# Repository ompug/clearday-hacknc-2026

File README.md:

# Clearday

A social money app for roommates, built at HackNC 2026. Upcoming bills float as glossy Frutiger Aero bubbles you pop when they are paid. Shared expenses split through a real ledger and update live for everyone in the household. A Monte Carlo "money weather" forecast warns of tight weeks before they happen, and Clearday Home (an Arduino UNO Q with a smart bulb) reacts to the household in real time.

Clearday is an independent hackathon project. It is not affiliated with or endorsed by Capital One. The demo runs entirely on seeded sandbox and synthetic data.

## What it does

- **The sky.** Each bill is a bubble; height shows how soon it is due and the icon plus label shows whether the forecast says you can cover it. A list view is the screen-reader default.
- **Live shared bubbles.** Rent, electric and internet are shared. Popping a share pays through a Nessie transfer and the ledger; every roommate's screen (and the bulb) updates over Socket.IO.
- **Money weather.** A 30-day forecast with a plain-words chance of dipping below your cushion, safe-to-spend, and a labeled backtest number.
- **Split with words.** "Split last night's pizza with Jake and Priya": Gemma finds the purchase through narrow tools, the server computes every amount, and you confirm.
- **Receipt itemizing and price memory.** Scan a receipt, fix the items, split by item with tax and tip, and see "cheaper before" hints.
- **Also built:** unusual-charge and duplicate-subscription detection, an ElevenLabs household announcement with transcript, a weekly recap, an amount-free private feed, a hypothetical 10-year Future view, a synthetic-household analyst view, and a private opt-in help panel with NC resources.

| Forecast | Split proposal |
| --- | --- |
|  |  |

| Receipt split | List view | Private feed |
| --- | --- | --- |
|  |  |  |

## Architecture

```
web/        Next.js + TypeScript + Tailwind + Framer Motion (responsive)
api/        FastAPI + python-socketio; owns every secret and external call
analytics/  Pure Python modules (forecast, categorize, detection, ...)
device/     Clearday Home: Linux-side Python (bulb, keypad, audio) + MCU sketch (LED matrix)
scripts/    dev.sh, seed_nessie.py, reset_demo.py, demo_rehearsal.py, E2E and audit tooling
docs/       Proposal, technical spec, security, hardware, build plan, demo script
```

- **web** talks only to the API (or an in-memory mock with `NEXT_PUBLIC_USE_MOCKS=1`).
- **api** is the only component that calls Nessie, Gemma and ElevenLabs. Nessie data is cached in the database; the demo reads from the cache.
- **Database:** TimescaleDB, local in podman/Docker (`docker-compose.yml`) for dev and the demo. A Tiger Cloud target (`DB_TARGET=tiger`) exists as an optional backup.
- **device** gets data only from `/api/device/summary` and `/api/household/status`, with a revocable device token. The bulb is driven through Home Assistant.
- **analytics:** `forecast`, `detection`, `backtest` and `synthetic_data` are the stats teammate's real models; `categorize`, `prices`, `cohorts` and `future` are still stubs returning deterministic data behind the exact contract signatures, and `splits` (the ledger math) is real.
- **Hosting:** local only. The demo runs the API, web and database on one laptop.

## Run it

Requires Python 3.12 (installed by bootstrap via uv), Node, and podman-compose or Docker Compose.

```bash
bash scripts/bootstrap.sh          # uv sync, git hooks (idempotent)
cp api/.env.example api/.env       # fill in your own keys; api/.env is gitignored
cp web/.env.example web/.env.local # set NEXT_PUBLIC_USE_MOCKS=0 to use the API
(cd web && npm install)
bash scripts/dev.sh up             # DB, API on :8000, web on :3001 (logs/ has output)
```

Other commands:

```bash
bash scripts/dev.sh status | down | restart
uv run python -m scripts.reset_demo        # return DB and Nessie records to the seeded state
bash scripts/dev.sh rehearse               # cold start, reset, walk every demo beat
uv run pytest && uv run ruff check         # Python tests and lint
(cd web && npm run check)                  # typecheck, lint, format
(cd device && uv sync && uv run pytest)    # device tests
```

`api/.env` holds the Nessie, ElevenLabs and model (Gemma, any OpenAI-compatible endpoint with tool calling) settings. Without a model endpoint the assistant falls back to a template; without ElevenLabs the announcement is text only.

## System design

Sources are in `docs/img/design/`; re-render with `uv run python docs/img/design/render.py`.

## Security and privacy

- **Money is integer cents everywhere.** Leftover cents use the largest-remainder method with ties broken by user ID, and totals reconcile to the cent. Nessie's whole-dollar amounts are converted only at the Nessie client boundary. `scripts/check_money.sh` lints for float money in the pre-commit hook.
- **Identity comes from the session cookie or device token**, never from request bodies or model output. Socket.IO connections without one are rejected.
- **Payments carry a client-generated idempotency key**, enforced by a unique constraint.
- **Model tool contract.** Gemma may call only `find_purchase`, `list_household_members`, `propose_split`, `explain_forecast`, `explain_anomaly` and `read_receipt`, with capped fields, rows and dates and at most 3 calls per request. It never sees raw history, account numbers, Nessie IDs or other people's real names. It proposes; the server recomputes every amount from the ledger; the user confirms. The audit log stores fields and row counts, never values. Merchant names, memos and receipt text are treated as untrusted data.
- **No amounts in the feed or on Clearday Home.** The device speaks household-level information only, without names by default.
- **Receipt images are deleted** right after extraction.
- **Secrets stay in `api/.env`** (gitignored); a pre-commit guard blocks staged secret values. Account views show a nickname and last 4 digits only.
- The analyst view uses synthetic households and hides segments under 20; the Future view is labeled "Hypothetical, not investment advice".

See `docs/03-security-and-privacy.md` for the full rules.

## Accessibility

WCAG AA contrast (audited on glass with axe via `scripts/ui_audit.py`), every bubble state has an icon and a text label, bubbles are real buttons with accessible names, full keyboard access with visible focus, a list view for screen readers, `prefers-reduced-motion` plus an in-app toggle, a text-size control that survives 200% zoom, and transcripts for all audio.

## Credits

- **Nessie**, Capital One's hackathon API, for the sandbox customers, accounts, purchases, bills and transfers.
- **ElevenLabs** for the household announcement and recap voices.
- **Google's Gemma** open model for natural-language splits and receipt reading.
- **TimescaleDB** (Tiger Data) for the time-series database.
- **Home Assistant** for driving the smart bulb.
- Built for HackNC 2026. Palette is inspired by, but not affiliated with, Capital One. All artwork is original.

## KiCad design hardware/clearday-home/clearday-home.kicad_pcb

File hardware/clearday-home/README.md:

# Clearday Home

Rev A, 2026-10-11, HackNC 2026. A USB-powered kitchen-counter companion for
the Clearday roommate bill-splitting app. It uses light and short spoken
announcements, with no display and no dollar amounts shown on the device.

Open **`clearday-home.kicad_pro` in KiCad 8**. The five-sheet schematic, BOM,
and PDF are complete. The 70 mm PCB is an **unrouted placement study, not a
manufacturing release**. The board and review Gerbers must not be fabricated.

## Files and verification

- `clearday-home.kicad_sch`: Power & USB and links to four child sheets.
- `mcu.kicad_sch`, `leds.kicad_sch`, `audio.kicad_sch`, `inputs.kicad_sch`:
  MCU, LEDs, Audio, and Inputs & Expansion.
- `clearday-home.kicad_pcb`: two-layer placement study with assigned nets,
  twelve edge LEDs, rear service components, and ground pours on both layers.
- `clearday-home.pdf`: five-page schematic export.
- `bom.csv`: grouped references, quantity, value, exact MPN, footprint,
  manufacturer, and assembly notes for 78 components.
- `erc.rpt`: KiCad **8.0.9**, zero errors and zero warnings; no exclusions.
- `drc.rpt`: 72 PCB violations and 122 unconnected items. Not a pass.
- `clearday-home.xml` and `validation.json`: exported connectivity and checks
  of all 295 numbered PCB pads against the schematic, plus critical pin maps.
- `fab/`: front/back PNGs, SVGs, and explicitly labeled unrouted review Gerbers.
- `generate.py`, `validate.py`, `validate.sh`, `export-review.sh`: reproducible
  generation, checking, and export. `design.json` is generator metadata.
- `SOURCING.md`: part availability evidence and datasheet references.

All footprints are from KiCad 8 standard libraries. Symbols are standard
except the local TPS22918 and a corrected copy of the standard MAX98357A.
The latter sets exposed pad 17 to power input rather than unspecified, as the
datasheet requires it to connect to ground. No electrical check is suppressed.
See `LIBRARIES.md` for attribution. The project library tables use KiCad 8
environment variables, not machine-specific absolute paths.

## Circuit blocks

**Power & USB.** J1 is a GCT USB4105-GF-A 16-pin USB 2.0 Type-C receptacle.
Separate 5.1 kΩ resistors terminate CC1 and CC2. Their voltages reach ADC1
through 10 kΩ / 10 nF filters for source-current detection. U2 protects the
data pair, with both orientations of the receptacle wired together. R3/R4
are 22 Ω series resistors intended near the MCU. F1 is a 2 A hold PTC;
U3 is a 1 A AP7361C-33E 3.3 V LDO with input/output capacitors. D1 indicates
3.3 V power. The USB shell is bonded to ground.

**MCU.** U1 is ESP32-S3-WROOM-1-N8R8, with 8 MB flash and 8 MB octal PSRAM.
Native USB supports programming and USB serial; UART0 is also available on
J5. EN has a 10 kΩ / 1 µF reset network and reset switch. GPIO0 has a 10 kΩ
pull-up and BOOT switch. Hold BOOT, tap RESET, then release BOOT for ROM
download mode. Unused pins have no-connect markers. GPIO3/45/46 are unloaded;
GPIO35/36/37 are reserved for PSRAM and unconnected.

**LEDs.** D2 through D13 are WS2812B-V5/W RGB pixels, each with 100 nF
decoupling. U5 converts GPIO4's 3.3 V data to 5 V logic, followed by a 330 Ω
series resistor. U6 switches the LED supply and its 1000 µF reservoir.
A 10 nF CT capacitor gives roughly 26 ms rise time at 5 V. QOD is deliberately
unconnected, so the 1000 µF capacitor does not discharge through the switch's
internal discharge device. Firmware keeps data low while power is off, then
waits at least 50 ms after LED_ENABLE before transmitting. The ring itself
is the light; no smart-bulb bridge is included.

**Audio.** MAX98357A U4 drives a floating 4–8 Ω speaker through JST-PH J2.
Use a speaker rated around 3 W. Neither terminal is ground. R15's 100 kΩ
connection to VDD selects +3 dB gain. R13's 560 kΩ resistor from AMP_ENABLE
and the amplifier's internal 100 kΩ pulldown produce nominally 0.500 V on
SD_MODE, selecting `(left + right) / 2`; a low GPIO shuts it down. A 100 kΩ
external enable pulldown mutes at reset. Output power depends on impedance,
supply voltage, digital level, and distortion; a 3 W speaker rating does not
mean the board delivers 3 W continuously.

MK1 is an ICS-43434 bottom-port microphone, powered from 3.3 V. LR is grounded
for the left slot, and a 100 kΩ data pulldown defines the high-impedance slot.
The ESP32 supplies shared BCLK/LRCLK to both audio ICs. A suitable starting
configuration is 48 kHz, two 32-bit slots, 3.072 MHz BCLK, with 24 significant
microphone bits. The amplifier and microphone have separate data nets and
need no MCLK. Keep the acoustic hole open and isolate the mic from speaker
vibration. Future voice commands still require firmware and an app privacy flow.

**Inputs & expansion.** SW3 is a 12 mm acknowledge switch. J3 accepts a
parallel external passive arcade button. R17, R18, and C28 filter BTN_ACK:
about 0.9 ms press and 10 ms release time constants; pressed voltage is
approximately 0.3 V. Require 30 ms stable state in firmware. J4 provides
Qwiic/STEMMA QT I2C with 4.7 kΩ pull-ups and local decoupling. Start at
100 kHz, budget at most 50 mA for sensors, and check the combined pull-up
resistance when attaching a board with its own pull-ups.

## GPIO map

| GPIO | Net | Direction / purpose |
| --- | --- | --- |
| 0 | BOOT | Boot strap and service switch only |
| 1 | CC1_SENSE | ADC input for Type-C source-current indication |
| 2 | CC2_SENSE | ADC input for Type-C source-current indication |
| 4 | LED_DATA | Output to 74AHCT1G125 |
| 5 | BTN_ACK | Active-low button input |
| 8 | I2C_SDA | Bidirectional, 3.3 V |
| 9 | I2C_SCL | I2C clock, 3.3 V |
| 10 | I2S_BCLK | Output to amplifier and microphone |
| 11 | I2S_LRCLK | Output to amplifier and microphone |
| 12 | I2S_DOUT | Output to amplifier DIN |
| 13 | I2S_DIN | Input from microphone SD |
| 14 | AMP_ENABLE | High selects mixed audio; low shuts down |
| 16 | LED_ENABLE | High enables U6 slow start |
| 19 | USB_DN | Native USB D− |
| 20 | USB_DP | Native USB D+ |
| 43 | UART_TX | UART0 output |
| 44 | UART_RX | UART0 input |

## Connector pinouts

| Connector | Pinout |
| --- | --- |
| J2 speaker | 1 SPK_P, 2 SPK_N; neither grounded |
| J3 external button | 1 BTN_RAW, 2 GND; short with passive switch only |
| J4 Qwiic | 1 GND, 2 3V3, 3 SDA, 4 SCL |
| J5 custom service | 1 3V3, 2 GND, 3 TX, 4 GND, 5 RX, 6 GND, 7 EN, 8 GND, 9 BOOT, 10 GND |

J5 is a 2×5, 1.27 mm **custom UART header, not ARM SWD**. TX and RX are named
from the MCU perspective. Use 3.3 V logic and open-drain EN/BOOT control.
Its 3V3 pin is a reference; do not power the board from it while USB is present.

## App behavior and firmware contract

The intended device firmware connects over Wi-Fi to the app's Socket.IO
server, authenticates for one household, and receives semantic states:

| App state | Device output |
| --- | --- |
| clear | Steady soft blue: bills on track |
| tight week | Amber: a tight week ahead |
| celebration | Brief rainbow burst, then return to the current state |

Short announcements use the speaker. The app must show the same announcement
as an on-screen transcript, including when audio is muted. BTN_ACK acknowledges
the current notification and can stop speech. Do not include dollar amounts
in device announcements. Device messages should carry a household ID, event
ID, semantic state, and expiry so firmware can reject stale or duplicate
notifications. A disconnect should not leave a stale blue state indefinitely.

This is an intended contract, not an implemented API integration. Socket.IO
requires its Engine.IO/Socket.IO framing; a plain WebSocket client alone is
insufficient. Event names, authentication, pairing, reconnect behavior,
announcement transport, and acknowledgement semantics need agreement with
the app. No app or firmware files were changed by this hardware work.

## Power budget and board work remaining

Use a regulated **5 V / 3 A Type-C supply** for full operation. There is no
USB PD controller. CC pulldowns do not authorize an arbitrary current draw.
Firmware must classify the active CC voltage with ADC calibration and USB-C
thresholds, account for USB configuration/suspend where applicable, and cap
LED brightness and audio level to the available current. ADC sensing and
soft start are provided; that policy is not implemented here. Treat a PC
port as a restricted programming source until this has been validated.

For budgeting, reserve up to 720 mA for twelve legacy-compatible RGB pixels
at full white, about 700 mA for loud 4 Ω audio, and 500 mA for MCU peaks plus
sensor headroom. The selected V5 LEDs generally need less than that legacy
allowance. Avoid simultaneous maximum loads: the 2 A PTC derates with
temperature. At 300 mA, the LDO dissipates about 0.51 W; its 1 A electrical
rating is not a continuous thermal guarantee in a closed dome. Thermal
copper, Wi-Fi current transients, USB attach/inrush/suspend, and brownout
behavior need bench validation.

The PCB has no signal or supply traces yet. The provisional placement uses
a 60 mm LED circle inside a 70 mm board. LEDs leave a 90-degree antenna gap
and a smaller USB-shell gap; a perfectly uniform ring is not achieved in
this study. Review that optical tradeoff under the dome. USB, speaker
connector, and button face the back. The standard ESP32 footprint's antenna
keepout is retained. Ground pours are filled but are not a completed return
path design.

Before fabrication: route and verify USB at 90 Ω differential impedance for
the selected stackup; route power for the load budget; shorten decoupler
connections; keep I2S away from speaker outputs; add ground stitching;
resolve every DRC finding; review the module's 0.2 mm thermal-via drills
against fabricator capabilities; inspect footprint-mismatch reports after
rotation/mirroring; finish silkscreen; add mounting and enclosure details;
verify connector drawings and microphone sealing. Select the speaker,
cables, diffuser, power supply, and enclosure separately. No populated
prototype, RF/EMC testing, production procurement, or firmware is included.

## Reproduce the checks

With Docker installed, from the repository root:

```sh
bash hardware/clearday-home/validate.sh
bash hardware/clearday-home/export-review.sh
```

The first script pins the KiCad 8.0.9 image by digest, asserts a clean ERC,
exports the PDF/netlist, checks pad connectivity, and records DRC without
pretending the unrouted board passes. The second exports review-only
Gerbers/drills and requires ImageMagick `convert` for PNG rendering.

To regenerate the design, run `python3 generate.py` **inside that KiCad 8
container**, mounting this directory at `/work` and using it as the working
directory. Regeneration replaces the generated schematic, BOM, metadata,
project settings, and PCB, so preserve any later hand edits first. The
generator uses standard libraries supplied by that image and Python's
standard library plus KiCad's `pcbnew` module.

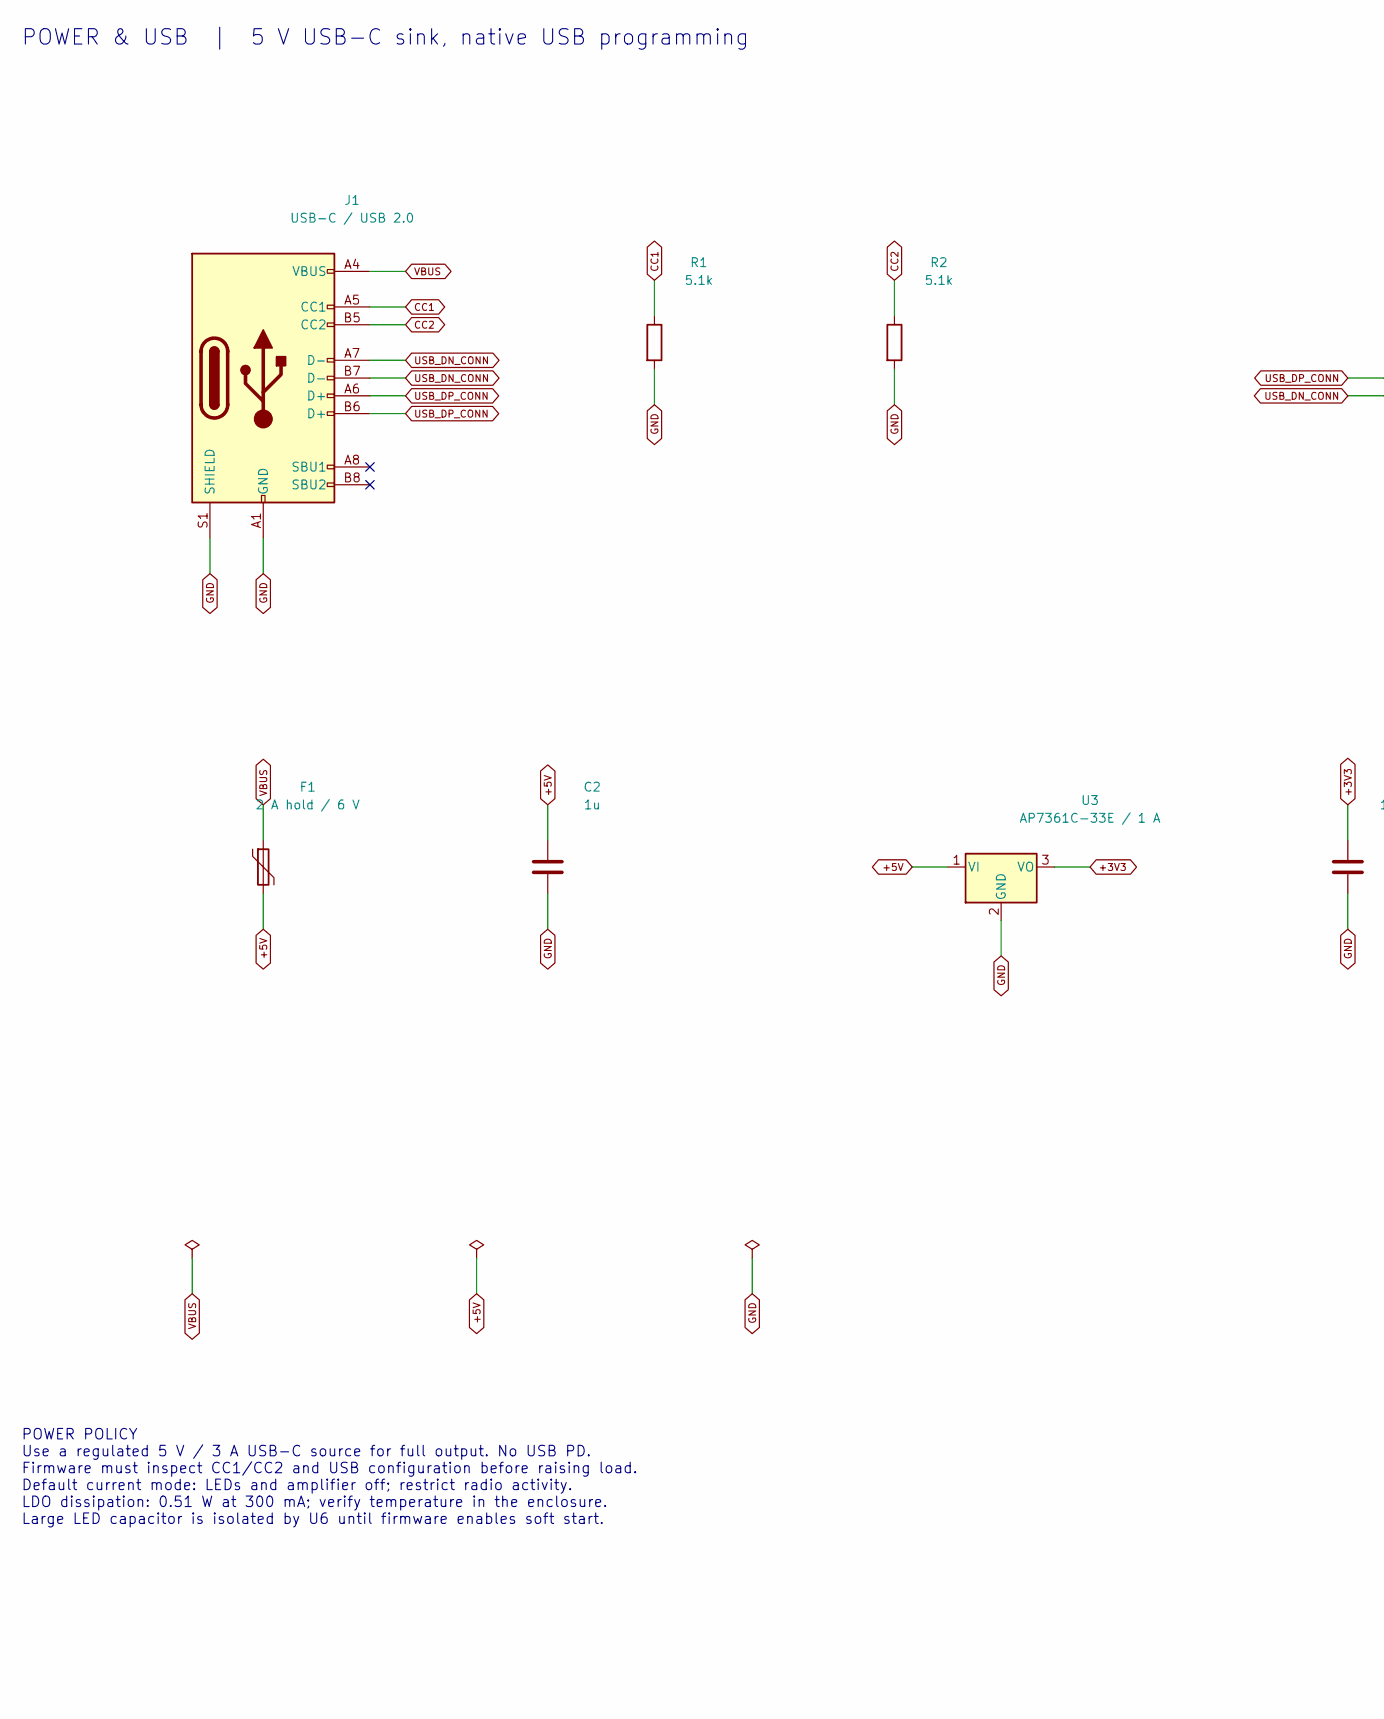
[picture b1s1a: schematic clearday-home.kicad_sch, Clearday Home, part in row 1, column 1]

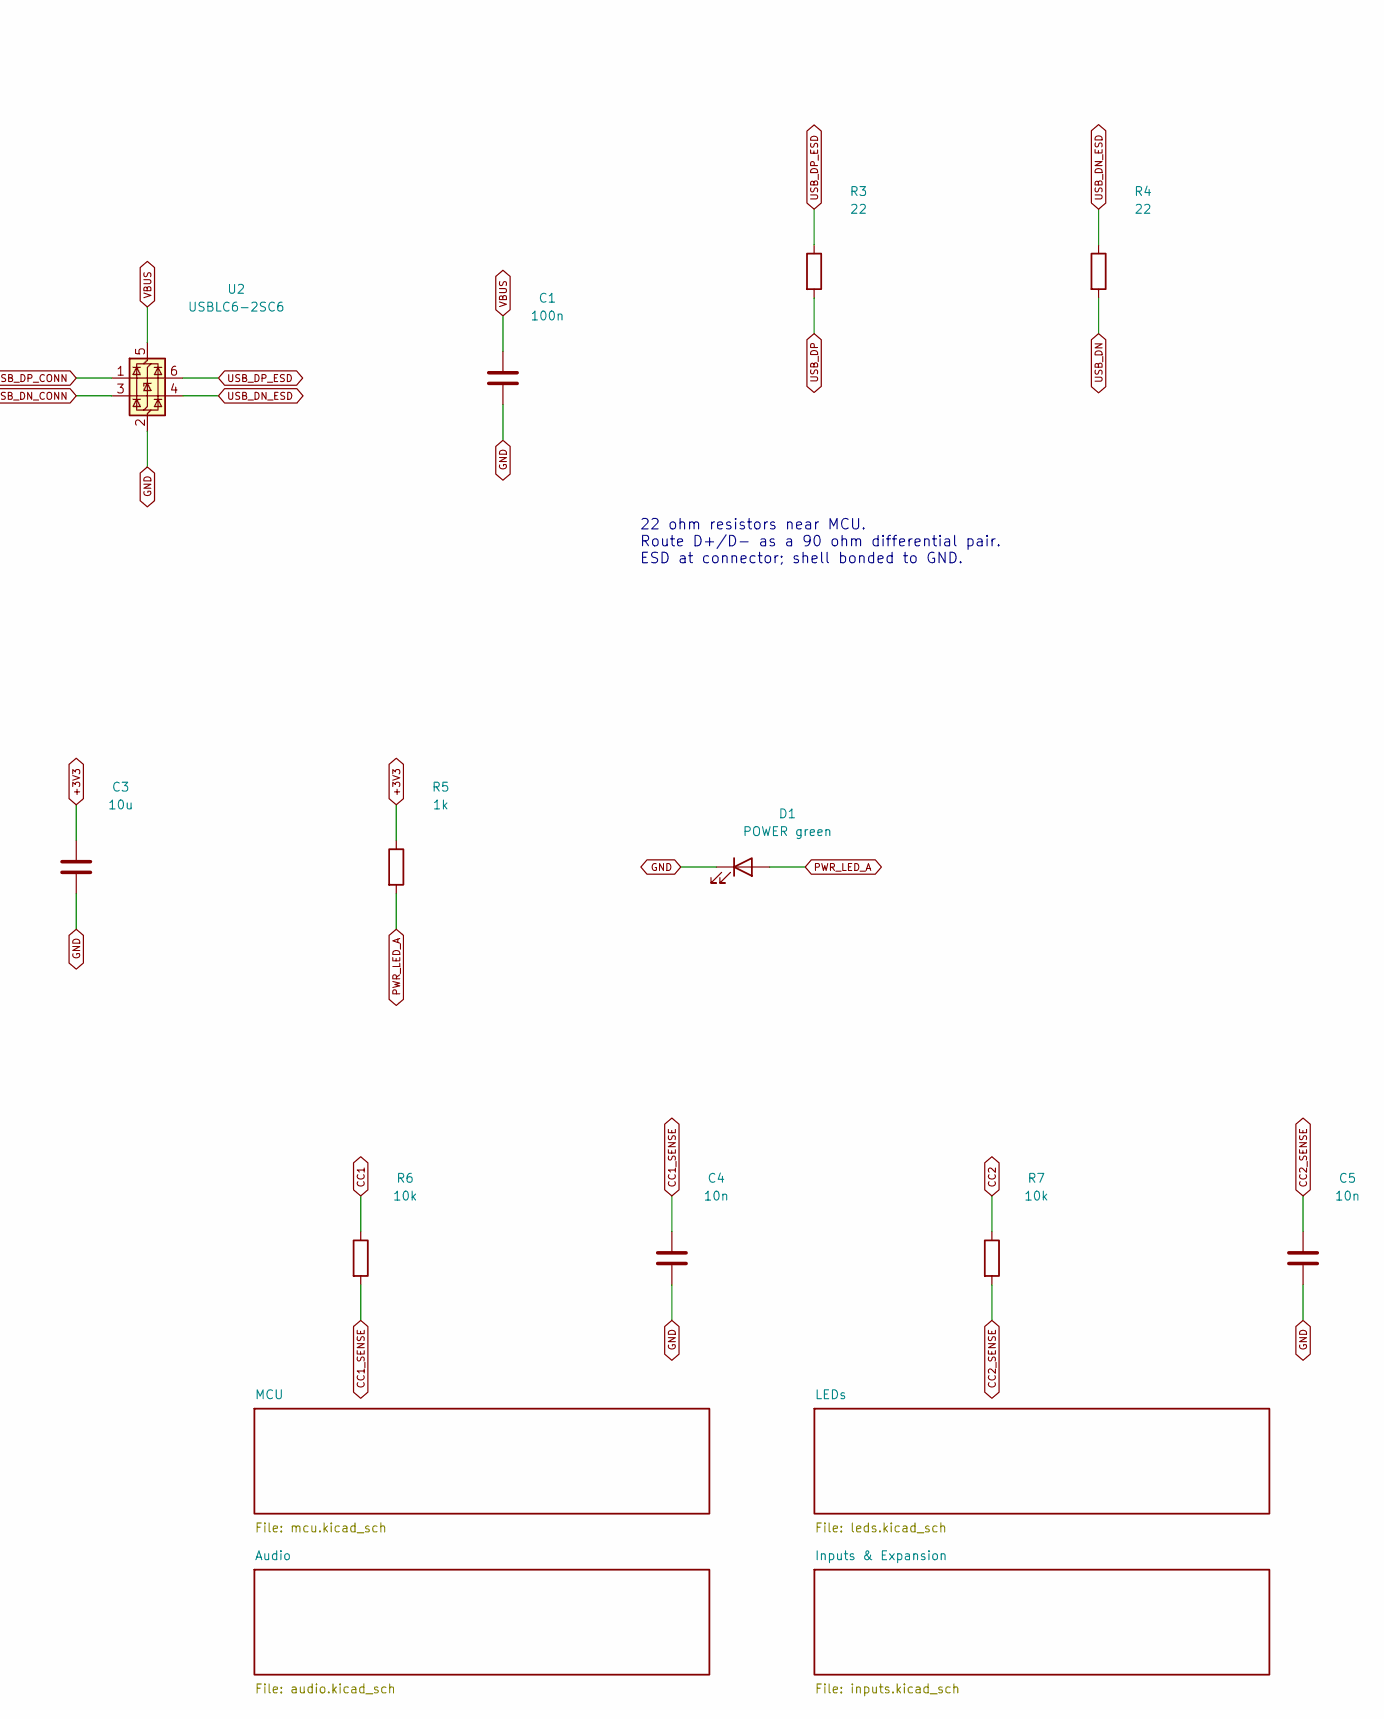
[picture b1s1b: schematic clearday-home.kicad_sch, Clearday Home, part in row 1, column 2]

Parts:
C1: 100n; C_0603_1608Metric; MPN GRM188R71C104KA01D
C2: 1u; C_0603_1608Metric; MPN GRM188R61A105KA61D
C3: 10u; C_0805_2012Metric; MPN GRM21BR61A106KE19L
C4, C5: 10n; C_0603_1608Metric; MPN GRM188R71H103KA01D
D1: POWER green; LED_0603_1608Metric; MPN LTST-C190KGKT
F1: 2 A hold / 6 V; Fuse_1206_3216Metric; MPN 1206L200/6
J1: USB-C / USB 2.0; USB_C_Receptacle_GCT_USB4105-xx-A_16P_TopMnt_Horizontal; MPN USB4105-GF-A
R1, R2: 5.1k; R_0603_1608Metric; MPN RC0603FR-075K1L
R3, R4: 22; R_0603_1608Metric; MPN RC0603FR-0722RL
R5: 1k; R_0603_1608Metric; MPN RC0603FR-071KL
R6, R7: 10k; R_0603_1608Metric; MPN RC0603FR-0710KL
U2: USBLC6-2SC6; SOT-23-6; MPN USBLC6-2SC6
U3: AP7361C-33E / 1 A; SOT-223-3_TabPin2; MPN AP7361C-33E-13

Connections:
+3V3: C3.1, R5.1, U3.3 (VO); also elsewhere on the board
+5V: C2.1, F1.2, U3.1 (VI); also elsewhere on the board
CC1: J1.A5 (CC1), R1.1, R6.1
CC1_SENSE: C4.1, R6.2; also elsewhere on the board
CC2: J1.B5 (CC2), R2.1, R7.1
CC2_SENSE: C5.1, R7.2; also elsewhere on the board
GND: C1.2, C2.2, C3.2, C4.2, C5.2, D1.1 (K), J1.A1 (GND), J1.A12 (GND), J1.B1 (GND), J1.B12 (GND), J1.S1 (SHIELD), R1.2, R2.2, U2.2 (GND), U3.2 (GND); also elsewhere on the board
PWR_LED_A: D1.2 (A), R5.2
USB_DN: R4.2; also elsewhere on the board
USB_DN_CONN: J1.A7 (D-), J1.B7 (D-), U2.3 (I/O2)
USB_DN_ESD: R4.1, U2.4 (I/O2)
USB_DP: R3.2; also elsewhere on the board
USB_DP_CONN: J1.A6 (D+), J1.B6 (D+), U2.1 (I/O1)
USB_DP_ESD: R3.1, U2.6 (I/O1)
VBUS: C1.1, F1.1, J1.A4 (VBUS), J1.A9 (VBUS), J1.B4 (VBUS), J1.B9 (VBUS), U2.5 (VBUS)

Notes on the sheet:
POWER & USB | 5 V USB-C sink, native USB programming
22 ohm resistors near MCU. Route D+/D- as a 90 ohm differential pair. ESD at connector; shell bonded to GND.
POWER POLICY Use a regulated 5 V / 3 A USB-C source for full output. No USB PD. Firmware must inspect CC1/CC2 and USB configuration before raising load. Default current mode: LEDs and amplifier off; restrict radio activity. LDO dissipation: 0.51 W at 300 mA; verify temperature in the enclosure. Lar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

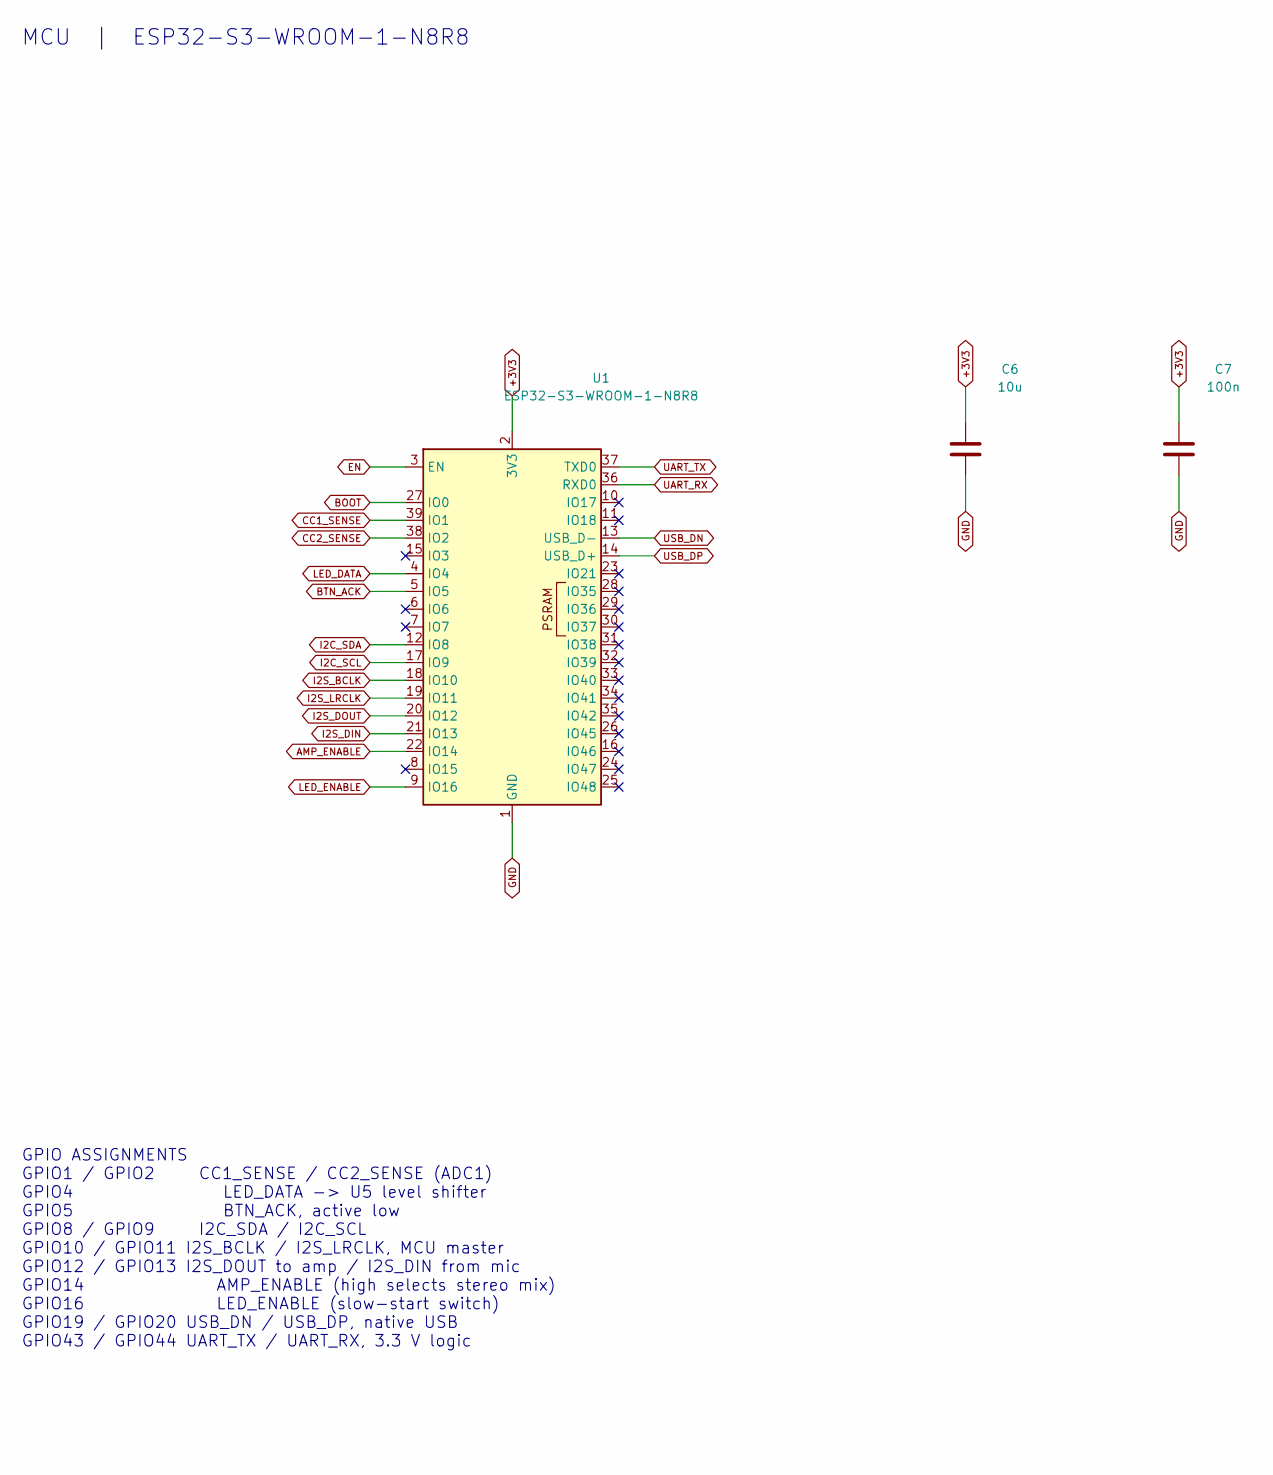
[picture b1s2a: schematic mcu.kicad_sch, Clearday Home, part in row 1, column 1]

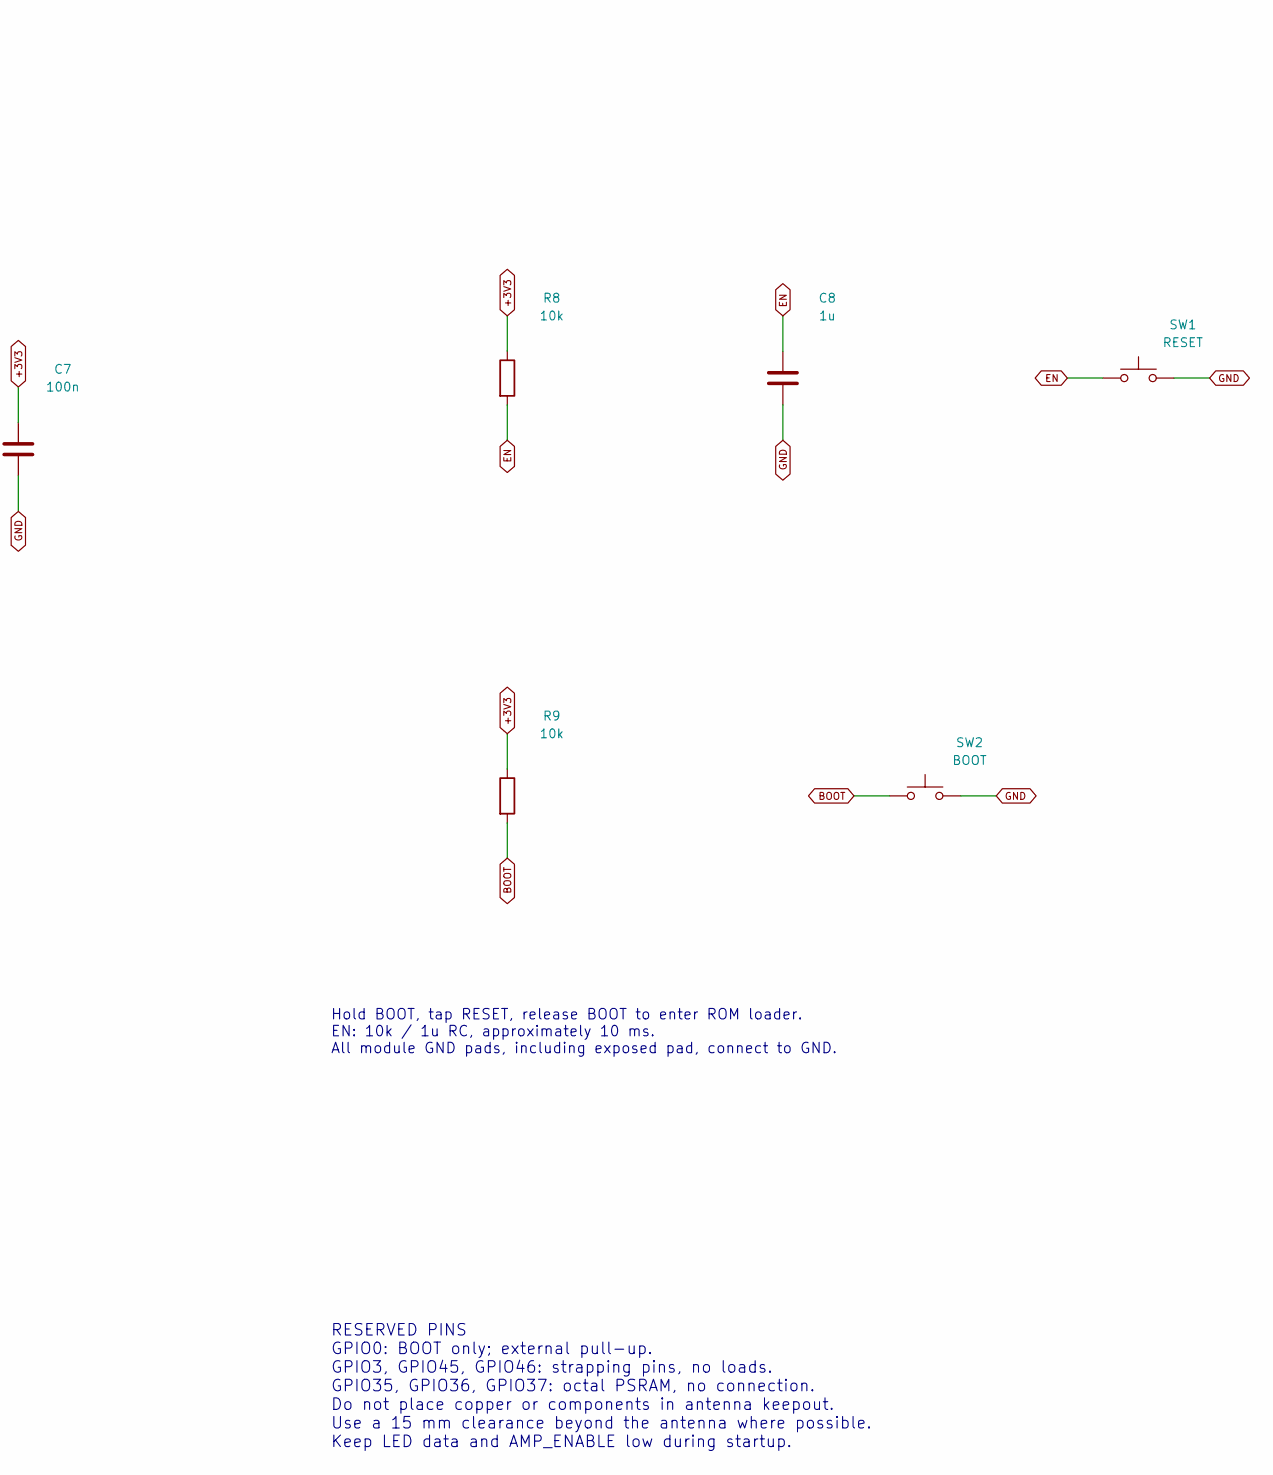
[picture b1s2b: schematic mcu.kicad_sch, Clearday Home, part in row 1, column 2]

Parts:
C6: 10u; C_0805_2012Metric; MPN GRM21BR61A106KE19L
C7: 100n; C_0603_1608Metric; MPN GRM188R71C104KA01D
C8: 1u; C_0603_1608Metric; MPN GRM188R61A105KA61D
R8, R9: 10k; R_0603_1608Metric; MPN RC0603FR-0710KL
SW1: RESET; SW_SPST_B3U-1000P; MPN B3U-1000P
SW2: BOOT; SW_SPST_B3U-1000P; MPN B3U-1000P
U1: ESP32-S3-WROOM-1-N8R8; ESP32-S3-WROOM-1; MPN ESP32-S3-WROOM-1-N8R8

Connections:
+3V3: C6.1, C7.1, R8.1, R9.1, U1.2 (3V3); also elsewhere on the board
AMP_ENABLE: U1.22 (IO14); also elsewhere on the board
BOOT: R9.2, SW2.1, U1.27 (IO0); also elsewhere on the board
BTN_ACK: U1.5 (IO5); also elsewhere on the board
CC1_SENSE: U1.39 (IO1); also elsewhere on the board
CC2_SENSE: U1.38 (IO2); also elsewhere on the board
EN: C8.1, R8.2, SW1.1, U1.3 (EN); also elsewhere on the board
GND: C6.2, C7.2, C8.2, SW1.2, SW2.2, U1.1 (GND), U1.40 (GND), U1.41 (GND); also elsewhere on the board
I2C_SCL: U1.17 (IO9); also elsewhere on the board
I2C_SDA: U1.12 (IO8); also elsewhere on the board
I2S_BCLK: U1.18 (IO10); also elsewhere on the board
I2S_DIN: U1.21 (IO13); also elsewhere on the board
I2S_DOUT: U1.20 (IO12); also elsewhere on the board
I2S_LRCLK: U1.19 (IO11); also elsewhere on the board
LED_DATA: U1.4 (IO4); also elsewhere on the board
LED_ENABLE: U1.9 (IO16); also elsewhere on the board
UART_RX: U1.36 (RXD0); also elsewhere on the board
UART_TX: U1.37 (TXD0); also elsewhere on the board
USB_DN: U1.13 (USB_D-); also elsewhere on the board
USB_DP: U1.14 (USB_D+); also elsewhere on the board

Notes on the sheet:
MCU | ESP32-S3-WROOM-1-N8R8
Hold BOOT, tap RESET, release BOOT to enter ROM loader. EN: 10k / 1u RC, approximately 10 ms. All module GND pads, including exposed pad, connect to GND.
GPIO ASSIGNMENTS GPIO1 / GPIO2 CC1_SENSE / CC2_SENSE (ADC1) GPIO4 LED_DATA -> U5 level shifter GPIO5 BTN_ACK, active low GPIO8 / GPIO9 I2C_SDA / I2C_SCL GPIO10 / GPIO11 I2S_BCLK / I2S_LRCLK, MCU master GPIO12 / GPIO13 I2S_DOUT to amp / I2S_DIN from mic GPIO14 AMP_ENABLE (high selects stereo mix) GP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
RESERVED PINS GPIO0: BOOT only; external pull-up. GPIO3, GPIO45, GPIO46: strapping pins, no loads. GPIO35, GPIO36, GPIO37: octal PSRAM, no connection. Do not place copper or components in antenna keepout. Use a 15 mm clearance beyond the antenna where possible. Keep LED data and AMP_ENABLE low duri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

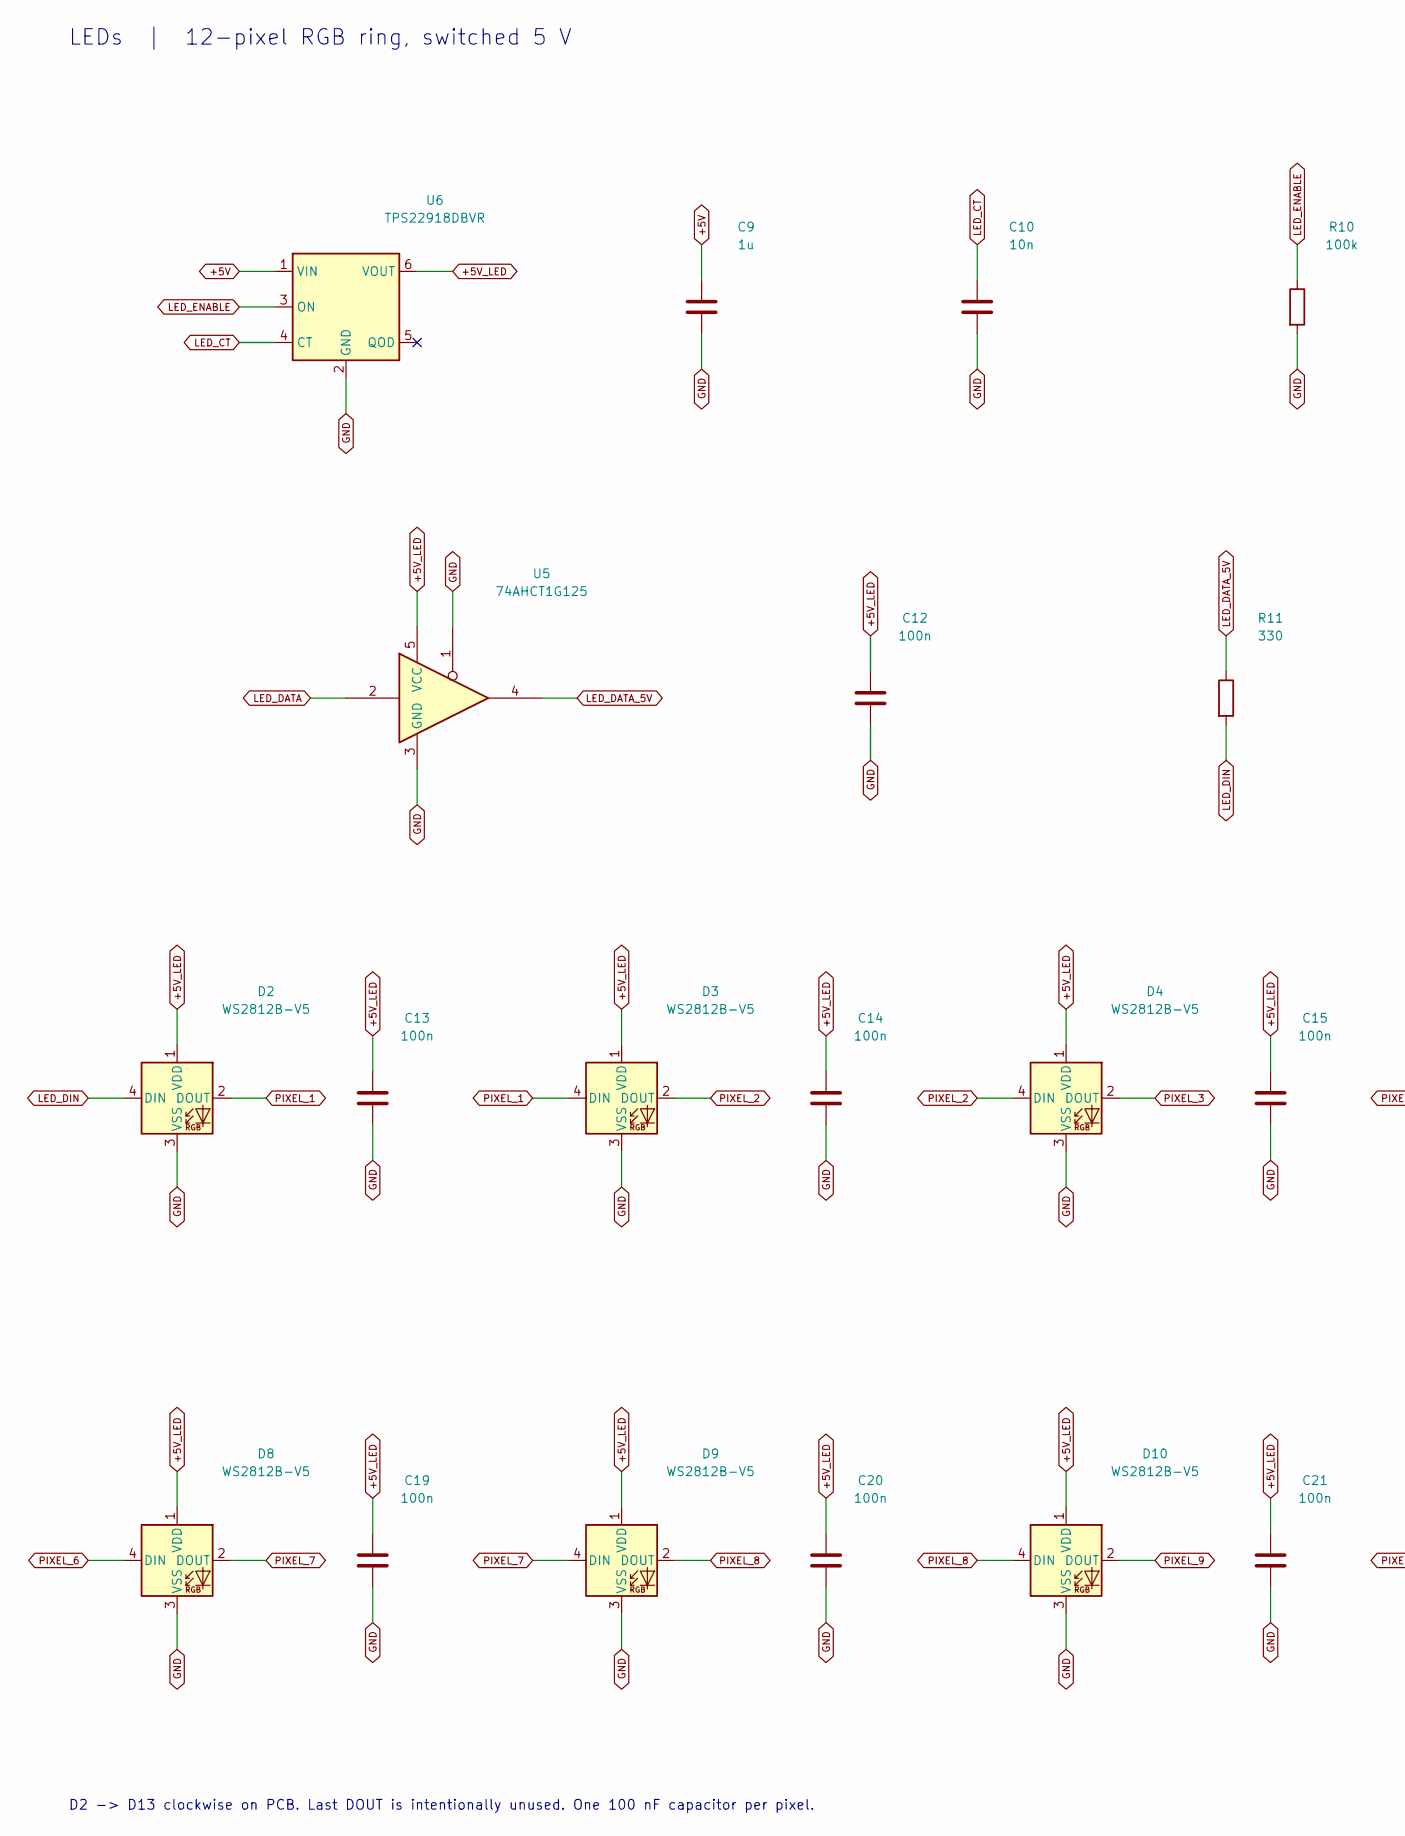
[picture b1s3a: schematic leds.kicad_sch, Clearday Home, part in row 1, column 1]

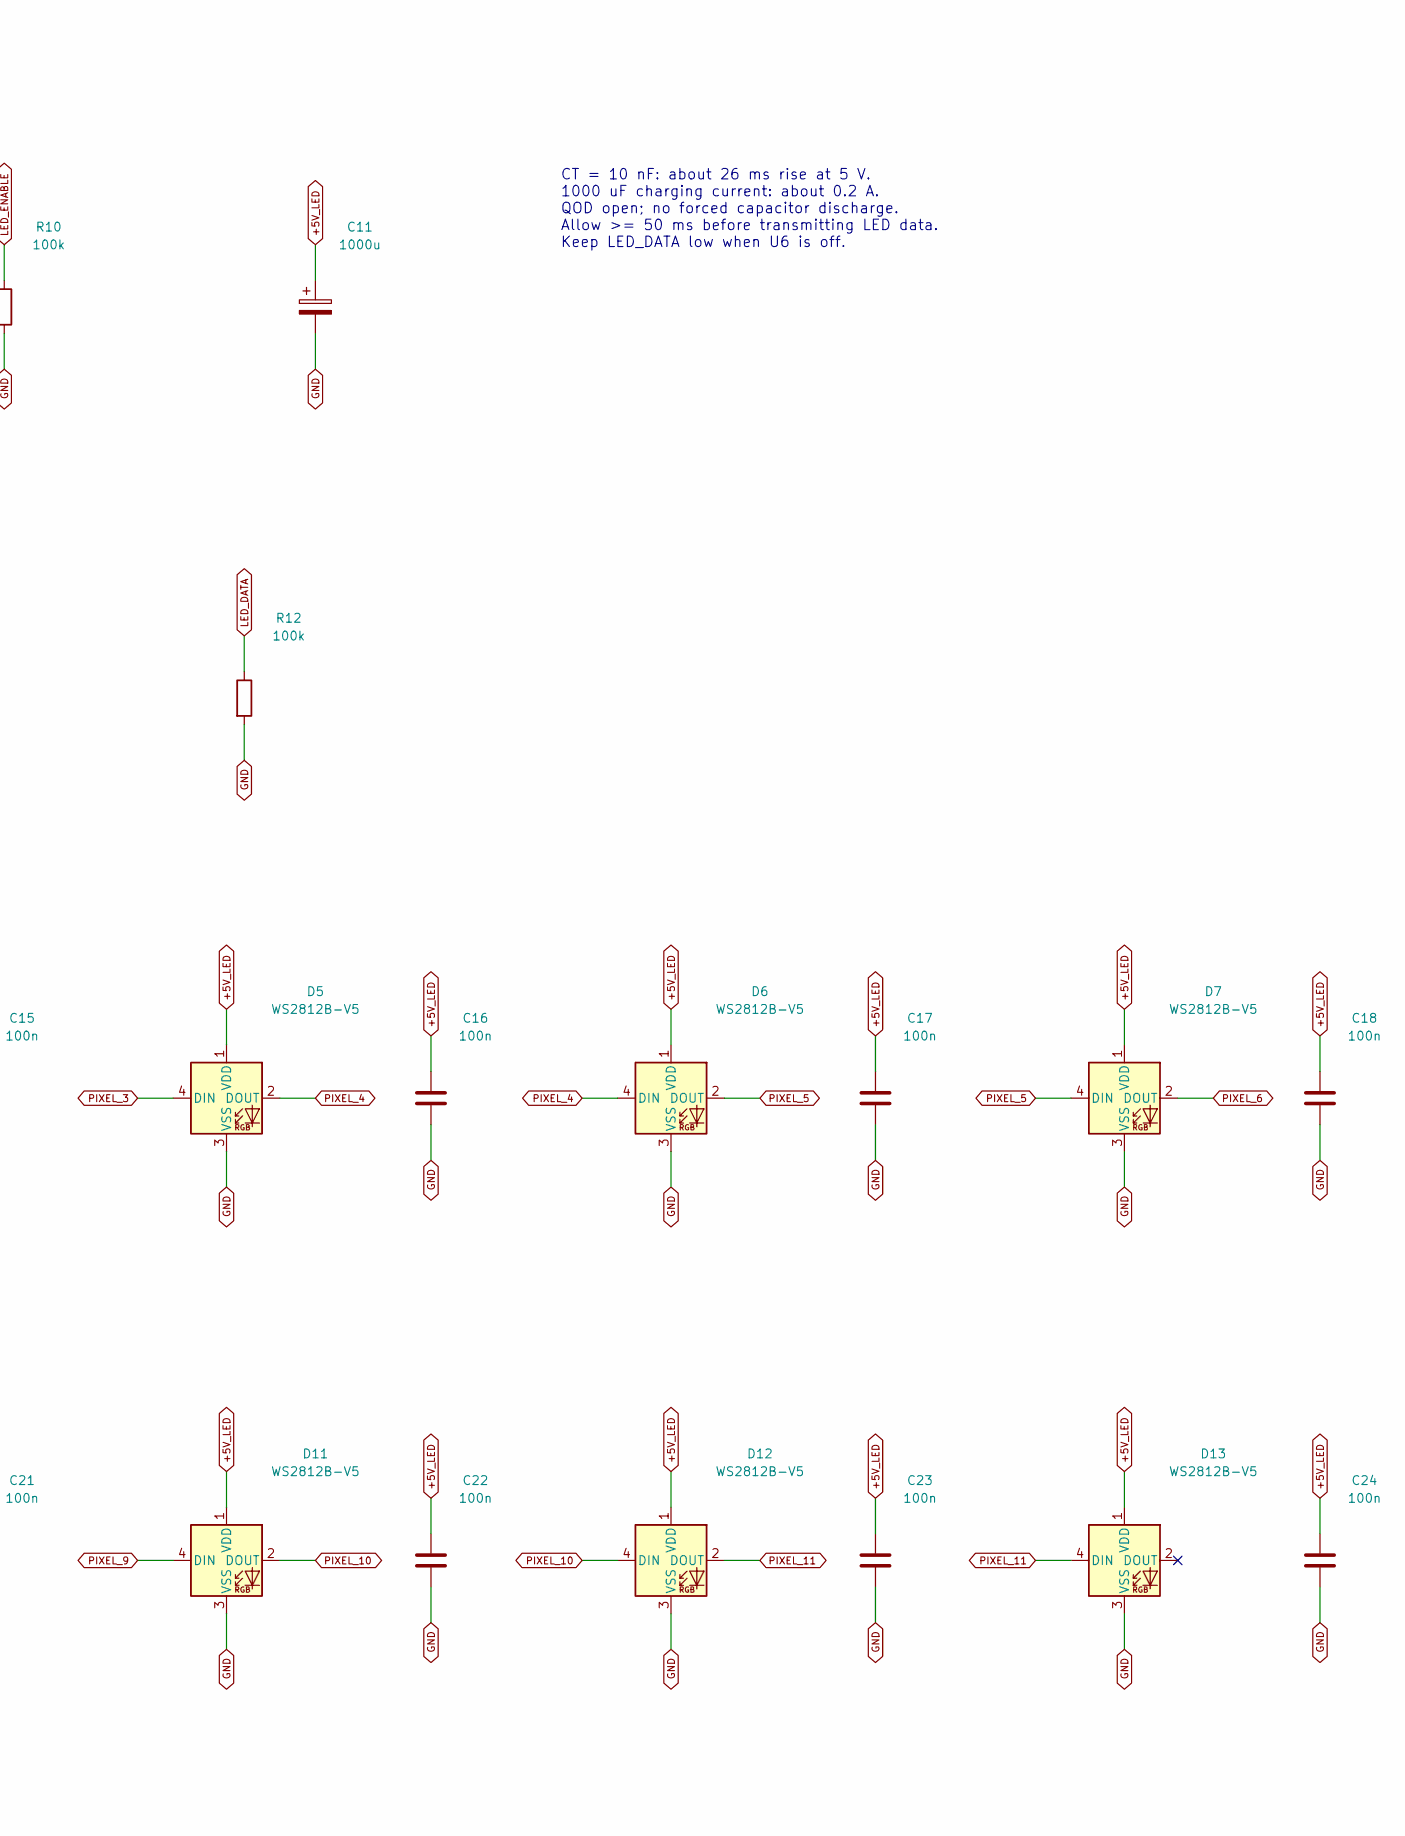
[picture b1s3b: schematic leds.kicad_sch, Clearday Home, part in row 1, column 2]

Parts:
C9: 1u; C_0603_1608Metric; MPN GRM188R61A105KA61D
C10: 10n; C_0603_1608Metric; MPN GRM188R71H103KA01D
C11: 1000u; CP_Radial_D10.0mm_P5.00mm; MPN EEU-FR1A102
C12, C13, C14, C15, C16, C17, C18, C19, C20, C21, C22, C23, C24: 100n; C_0603_1608Metric; MPN GRM188R71C104KA01D
D2, D3, D4, D5, D6, D7, D8, D9, D10, D11, D12, D13: WS2812B-V5; LED_WS2812B_PLCC4_5.0x5.0mm_P3.2mm; MPN WS2812B-V5/W
R10, R12: 100k; R_0603_1608Metric; MPN RC0603FR-07100KL
R11: 330; R_0603_1608Metric; MPN RC0603FR-07330RL
U5: 74AHCT1G125; SOT-23-5; MPN SN74AHCT1G125DBVR
U6: TPS22918DBVR; SOT-23-6; MPN TPS22918DBVR

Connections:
+5V: C9.1, U6.1 (VIN); also elsewhere on the board
+5V_LED: C11.1, C12.1, C13.1, C14.1, C15.1, C16.1, C17.1, C18.1, C19.1, C20.1, C21.1, C22.1, C23.1, C24.1, D2.1 (VDD), D3.1 (VDD), D4.1 (VDD), D5.1 (VDD), D6.1 (VDD), D7.1 (VDD), D8.1 (VDD), D9.1 (VDD), D10.1 (VDD), D11.1 (VDD), D12.1 (VDD), D13.1 (VDD), U5.5 (VCC), U6.6 (VOUT)
GND: C9.2, C10.2, C11.2, C12.2, C13.2, C14.2, C15.2, C16.2, C17.2, C18.2, C19.2, C20.2, C21.2, C22.2, C23.2, C24.2, D2.3 (VSS), D3.3 (VSS), D4.3 (VSS), D5.3 (VSS), D6.3 (VSS), D7.3 (VSS), D8.3 (VSS), D9.3 (VSS), D10.3 (VSS), D11.3 (VSS), D12.3 (VSS), D13.3 (VSS), R10.2, R12.2, U5.1, U5.3 (GND), U6.2 (GND); also elsewhere on the board
LED_CT: C10.1, U6.4 (CT)
LED_DATA: R12.1, U5.2; also elsewhere on the board
LED_DATA_5V: R11.1, U5.4
LED_DIN: D2.4 (DIN), R11.2
LED_ENABLE: R10.1, U6.3 (ON); also elsewhere on the board
PIXEL_1: D2.2 (DOUT), D3.4 (DIN)
PIXEL_2: D3.2 (DOUT), D4.4 (DIN)
PIXEL_3: D4.2 (DOUT), D5.4 (DIN)
PIXEL_4: D5.2 (DOUT), D6.4 (DIN)
PIXEL_5: D6.2 (DOUT), D7.4 (DIN)
PIXEL_6: D7.2 (DOUT), D8.4 (DIN)
PIXEL_7: D8.2 (DOUT), D9.4 (DIN)
PIXEL_8: D9.2 (DOUT), D10.4 (DIN)
PIXEL_9: D10.2 (DOUT), D11.4 (DIN)
PIXEL_10: D11.2 (DOUT), D12.4 (DIN)
PIXEL_11: D12.2 (DOUT), D13.4 (DIN)

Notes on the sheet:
LEDs | 12-pixel RGB ring, switched 5 V
CT = 10 nF: about 26 ms rise at 5 V. 1000 uF charging current: about 0.2 A. QOD open; no forced capacitor discharge. Allow >= 50 ms before transmitting LED data. Keep LED_DATA low when U6 is off.
D2 -> D13 clockwise on PCB. Last DOUT is intentionally unused. One 100 nF capacitor per pixel.
